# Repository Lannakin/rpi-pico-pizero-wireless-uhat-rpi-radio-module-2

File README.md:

# **wireless-uhat-tht-rpi-radio-module-2 - Design Notes**

## **CREDITS FOR FONTS**

[WebPlus_ToshibaSat_8x14 and WebPlus_ToshibaSat_9x16 by VileR](https://**int10h**.org/oldschool-pc-fonts/)
[scientifica © 2020 Akshay Oppiliappan (nerdy@peppe.rs)](https://github.com/oppiliappan/scientifica)

---

## **Overview**

This project is to adapt the Raspberry Pi Radio Module 2 (RM2) [(p/n RMC20452)](https://pip-assets.raspberrypi.com/categories/1216-raspberry-pi-radio-module-2/documents/RP-008943-DS-4-Radio%20Module%202%20Datasheet.pdf)
to the μHat specification, minus the EEPROM chip, as the RM2 is not compatible
with anything except the Raspberry Pi microcontrollers (RPIMCU).  The main
reason I am doing this is because I have an RP2350B A4 revision chip, which is
part of a Waveshare RP2350-PiZero board.  I wish I knew what the hell their
tables in the `40Pin OUT` section meant for sure.  Oh well, thank y'all for making
the schematic public.

**It should be noted that I am doing this as part of a hobby, and I am not any
kind of engineer.**

## **Schematic Notes**

- I've attempted to have PCB traces cross at 90° angles to help prevent / reduce
interference.

- I need to calculate how wide the traces and vias should be.

- I read or heard somewhere that it can be a good idea to basically have a
power rail border the board to prevent interference but I don't think I have
ever seen anyone do that.

## **Layout Considerations**

- Bottom layer is ground plane.

- Top layer is also a ground plane

- Top layer maybe should not be a ground plane.  I will look at the STMicro
Nucleo board design files and filch their secrets if they include the PCB design
files.

- The RM2 antenna has a big keep-out area.  I have positioned it roughly over
where the antenna on the Raspberry Pi Zero 2 W is located.  I hope it blocks the
HDMI / DVI connector, just to spite everyone.

  • Shit.  I just noticed the RP2350-PiZero has the stupid debug connector right
  under there.  22.3 mm from (top view) left edge of board to outside of DIO
  debug header insulation, 12.5 mm  from bottom edge of board to outside top of
  debug header insulation.

* The RM2 is now over the USB ports I guess

## **Component Notes**
<!-- Click on designators like R1, C5, U3 to highlight on PCB -->
- The RM2 is based on the CYW43439 and is made to share pins when used by the
RPIMCUs.

- Added LEDs for RM2 GPIO control.

- Considering adding a slot for debug port present on the RP2XX0-PiZero

## **Power Distribution**

Measuring traces on the W5500-EVB-Pico board as a reference.  Thanks Altium for
the online gerber viewer with a ruler.

| NET               | TRACE WIDTH       | CLEARANCE  |
|-------------------|-------------------|------------|
| 3V3DVC            | 0.8-0.9 mm        | 0.3 mm     |
| 5VDC VBUS VSYS    | 0.5 mm            | 0.3 mm     |
| GPIO              | 0.2 mm            | 0.2-0.3 mm |
| W5500             | 0.3 mm            | 0.2-0.3 mm |

## **References**

### DESIGN

[Pimoroni Pico Plus 2 W](https://cdn-shop.adafruit.com/product-files/6243/Pimoroni_Pico_Plus_2_W_Schematic.pdf)
[Raspberry Pi Pico 2 W](https://datasheets.raspberrypi.com/picow/pico-2-w-schematic.pdf)
[W5500-EVB-Pico](https://github.com/Wiznet/Hardware-Files-of-WIZnet/tree/master/02_iEthernet/W5500)
[Waveshare RP2350B-Plus-W](https://files.waveshare.com/wiki/RP2350B-Plus-W/RP2350B-Plus-W.pdf)

### PARTS

[Infineon CYW43439](https://www.mouser.com/datasheet/2/196/Infineon_CYW43439_DataSheet_v03_00_EN-3074791.pdf)
[RMC20452 aka Raspberry Pi Radio Module 2](https://pip-assets.raspberrypi.com/categories/1216-raspberry-pi-radio-module-2/documents/RP-008943-DS-4-Radio%20Module%202%20Datasheet.pdf)

---

### KiNotes - PCBtools.xyz

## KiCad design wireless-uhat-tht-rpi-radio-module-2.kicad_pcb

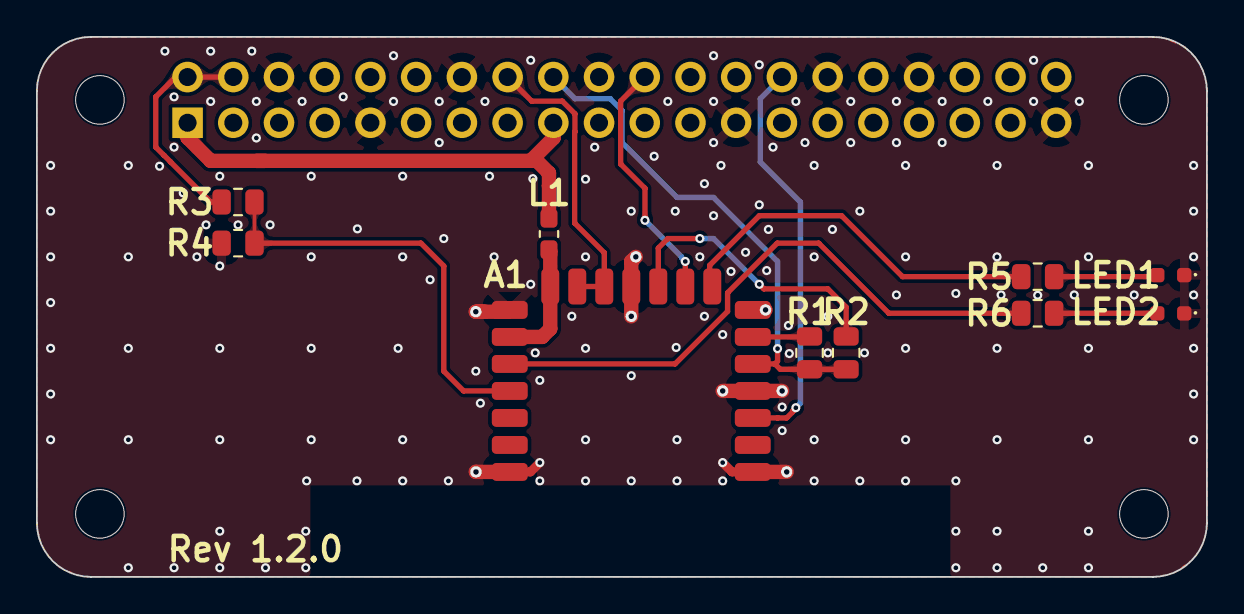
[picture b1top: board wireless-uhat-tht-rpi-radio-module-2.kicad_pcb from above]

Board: 2 copper layers, 65.0 x 30.0 mm, 15 parts (1 on the bottom side), 15 nets.

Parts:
A1: RMC20452; rpi_rmc20452t
J1: GPIO; PinSocket_2x20_P2.54mm_Vertical
L1: BLM18EG471SN1D; L_0603_1608Metric_Pad1.05x0.95mm_HandSolder
LED1: BU; LED_599-00XX-137F_0603_1608Metric
LED2: YL-GN; LED_599-00XX-137F_0603_1608Metric
MH1, MH2, MH3, MH4: MountingHole_2.7mm_M2.5
R1, R2: 10k; R_ERA-6A_0805_2012Metric
R3, R4, R5, R6: 470; R_ERA-6A_0805_2012Metric

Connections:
+3V3: J1.1, J1.17, L1.1
+5V: J1.2, J1.4, R3.1
/GPIO1: A1.3 (SCLK), J1.28
/GPIO23: A1.12 (WL_ON), A1.13 (BT_ON), J1.16
/GPIO24: A1.5 (DI), J1.18, R1.1, R2.1
/GPIO25: A1.9 (CS), J1.22
/WL_GPIO0: A1.8 (GPIO0), R5.2
/WL_GPIO1: A1.18 (GPIO1), R3.2, R4.1
/WL_GPIO2: A1.17 (GPIO2), R6.2
GND: A1.1 (GND), A1.4 (GND), A1.7 (GND), A1.11 (GND), A1.15 (GND), A1.21 (GND), J1.6, J1.9, J1.14, J1.20, J1.25, J1.30, J1.34, J1.39, LED1.1 (K), LED2.1 (K), R4.2
unnamed: A1.6 (DO), R1.2
unnamed: A1.14 (VDDIO), A1.16 (VIN), L1.2
unnamed: A1.10 (nIRQ), R2.2
unnamed: LED1.2 (A), R5.1
unnamed: LED2.2 (A), R6.1

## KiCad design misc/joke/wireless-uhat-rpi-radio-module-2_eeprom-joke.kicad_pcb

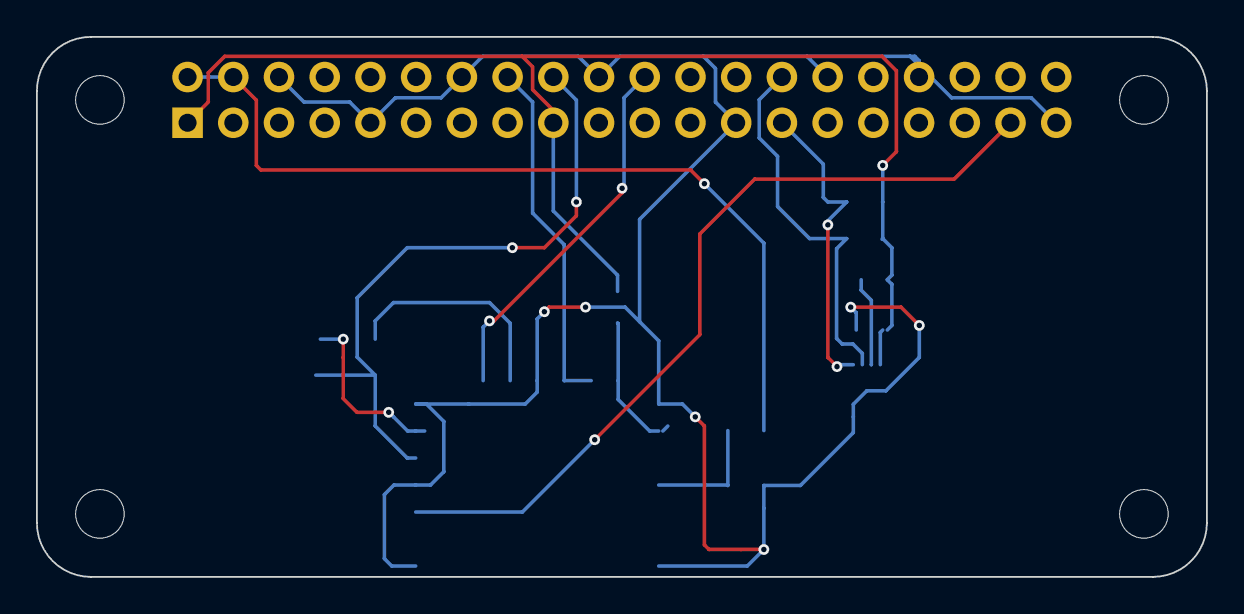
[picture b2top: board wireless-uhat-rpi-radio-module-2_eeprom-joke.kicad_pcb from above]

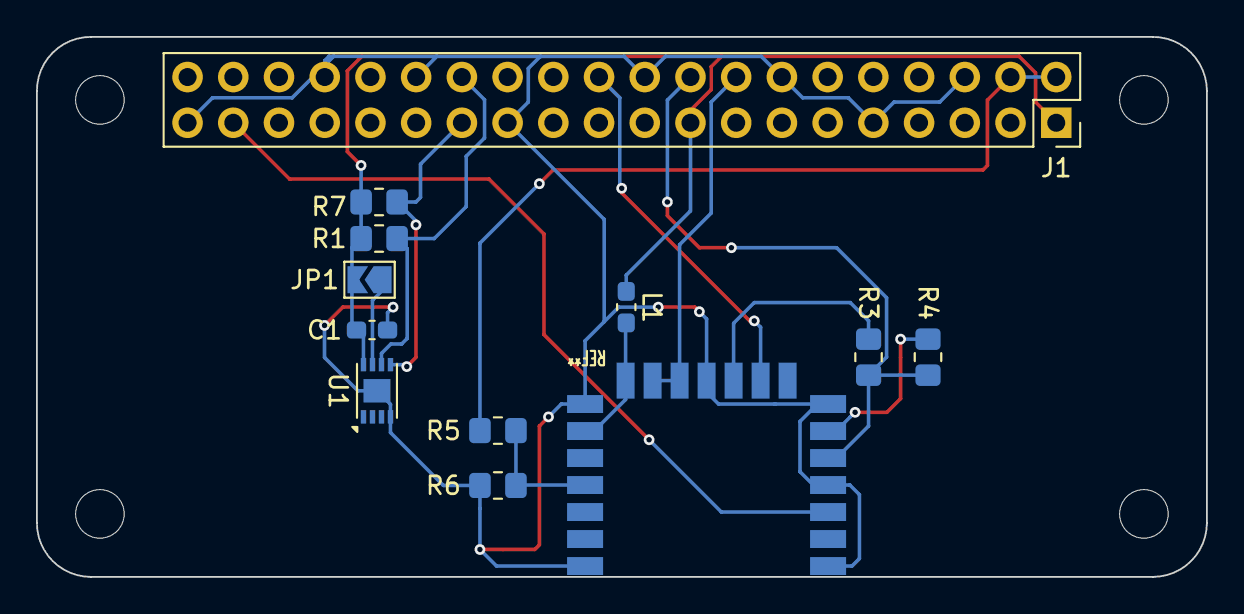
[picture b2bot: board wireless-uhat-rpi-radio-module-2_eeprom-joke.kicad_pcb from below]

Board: 2 copper layers, 65.0 x 30.0 mm, 16 parts (12 on the bottom side), 14 nets.

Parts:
C1: 0.1uF; C_0603_1608Metric_Pad1.08x0.95mm_HandSolder
J1: GPIO; PinSocket_2x20_P2.54mm_Vertical
JP1: ID_WP; SolderJumper-2_P1.3mm_Open_TrianglePad1.0x1.5mm
L1: BLM18EG471SN1D; L_0603_1608Metric_Pad1.05x0.95mm_HandSolder
MH1, MH2, MH3, MH4: MountingHole_2.7mm_M2.5
R1, R7: 3.9k; R_0805_2012Metric_Pad1.20x1.40mm_HandSolder
R3, R4: 470; R_0805_2012Metric_Pad1.20x1.40mm_HandSolder
R5, R6: 10k; R_0805_2012Metric_Pad1.20x1.40mm_HandSolder
U1: CAT24C256_EP; DFN-8-1EP_3x2mm_P0.5mm_EP1.3x1.5mm
U2: RMC20452; rpi_rmc20452t

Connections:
+3V3: C1.1, J1.1, J1.17, JP1.2 (B), L1.1, R1.1, R7.1, U1.8 (VCC)
+5V: J1.2, J1.4, R5.1
/GPIO0: J1.27, R7.2, U1.5 (SDA)
/GPIO1: J1.28, R1.2, U1.6 (SCL)
/GPIO23: J1.16, U2.12 (WL_ON), U2.13 (BT_ON)
/GPIO24: J1.18, R3.1, R4.1, U2.5 (DI)
/GPIO25: J1.22, U2.9 (CS)
/GPIO26: J1.37, U2.3 (SCLK)
/WL_GPIO1: R5.2, R6.1, U2.18 (GPIO1)
GND: C1.2, J1.6, J1.9, J1.14, J1.20, J1.25, J1.30, J1.34, J1.39, R6.2, U1.4 (GND), U1.9 (EP), U2.1 (GND), U2.4 (GND), U2.7 (GND), U2.11 (GND), U2.15 (GND), U2.21 (GND)
unnamed: JP1.1 (A), U1.7 (WP)
unnamed: R4.2, U2.6 (DO)
unnamed: L1.2, U2.14 (VDDIO), U2.16 (VIN)
unnamed: R3.2, U2.10 (nIRQ)

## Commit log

2026-02-14 tl;dr: initial commit
    =======================================================================
    added:
    .kinotes/ - notes
    KiNotes_wireless-uhat-rpi-radio-module-2.md
    settings.json
    todos.json
2026-02-19 tl;dr: make preparations to send board for prototyping
    =======================================================================
    added:
    misc/
    wireless-uhat-tht-rpi-radio-module-2.csv - i don't remember where
    this is from
    gerbers/ - gerbers for board; used OSH guidelines for now
2026-02-19 tl;dr: finishing touches to send board in for prototyping
    =======================================================================
    added:
    gerbers/
    wireless-uhat-tht-rpi-radio-module-2.7z - forgot to remove before
    commit
    -----------------------------------------------------------------------
2026-02-21 tl;dr: added fonts, moved RM2 module, switched to CC by-SA 4.0 license
    =======================================================================
    added:
    ./
    LICENSE - switched to CC by-SA license
    .kinotes/
    wireless-uhat-tht-rpi-radio-module-2_worklog_20260220.md - am i
2026-02-21 tl;dr: copied kinotes to README.md
    =======================================================================
    added:
    ./
    README.md - copied from kinotes. only the best for github :)
2026-02-21 tl;dr: debug connector zone was marked on the WRONG SIDE of the BOARD FFS moved RM2 further
    =======================================================================
    removed:
    .kinotes/
    wireless-uhat-rpi-radio-module-2_worklog_20260213.md - old
    -----------------------------------------------------------------------
    modified:
